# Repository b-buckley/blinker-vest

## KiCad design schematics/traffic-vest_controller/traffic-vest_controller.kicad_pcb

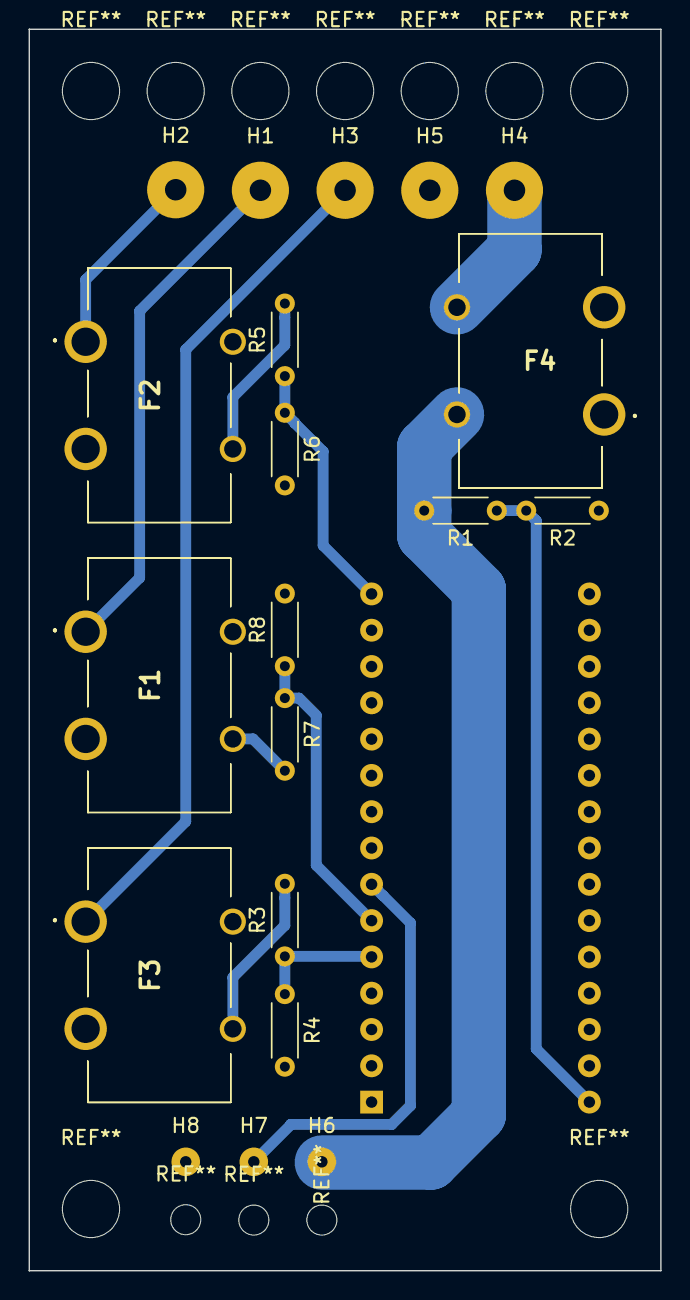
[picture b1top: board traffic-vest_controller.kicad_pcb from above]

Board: 2 copper layers, 44.2 x 86.9 mm, 21 parts (1 on the bottom side), 14 nets.

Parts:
A1: Arduino_Nano_v3.x; Arduino_Nano
F1, F2, F3: 1A; 35492
F4: 7.5A; 35492
H1: Bike Left; SolderWirePad_1x01_Drill1.5mm
H2: Bike Brake; SolderWirePad_1x01_Drill1.5mm
H3: Bike Right; SolderWirePad_1x01_Drill1.5mm
H4: Bike Power; SolderWirePad_1x01_Drill1.5mm
H5: Bike Ground; SolderWirePad_1x01_Drill1.5mm
H6: LED +12V; SolderWirePad_1x01_Drill0.8mm
H7: LED Data; SolderWirePad_1x01_Drill0.8mm
H8: LED GND; SolderWirePad_1x01_Drill0.8mm
R1: 100; R_Axial_DIN0204_L3.6mm_D1.6mm_P5.08mm_Horizontal
R2: 300; R_Axial_DIN0204_L3.6mm_D1.6mm_P5.08mm_Horizontal
R3, R5, R7: 20k; R_Axial_DIN0204_L3.6mm_D1.6mm_P5.08mm_Horizontal
R4, R6, R8: 10k; R_Axial_DIN0204_L3.6mm_D1.6mm_P5.08mm_Horizontal

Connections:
GNDREF: A1.4, A1.29, H5.1, H8.1, R2.1, R4.2, R6.2, R8.2
unnamed: A1.5, R3.1, R4.1
unnamed: A1.6, R7.1, R8.1
unnamed: A1.7, H7.1
unnamed: A1.15, R5.1, R6.1
unnamed: A1.30, R1.1, R2.2
unnamed: F1.1, H1.1
unnamed: F1.3, R7.2
unnamed: F2.1, H2.1
unnamed: F2.3, R5.2
unnamed: F3.1, H3.1
unnamed: F3.3, R3.2
unnamed: F4.3, H4.1
unnamed: F4.4, H6.1, R1.2

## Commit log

2022-02-21 Initial commit of code repo for Traffic Vest project for ELT-2720
2022-02-21 just playing with git
2022-03-09 Better late than never to start version tracking and stop sweating about version numbers
2022-03-09 Re-organized file tree, fixed paths in kidcad files, etc.
2022-03-09 added .gitignore
2022-03-10 Converted physical connectors to mounting holes; need to resize holes in PCB for wire sizes and spacing
2022-03-15 first add of schematics b/c of cached submodule weirdness. Includes updates as of converting connectors/mounting holes to generic pins with THT solder holes and matching strain-relief NPTHs. Also rea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
2022-03-15 Added dirty separate handling for each input signal as proof-of-concept.
2022-03-16 expanded board footprint to accomodate corner mounting holes; rearranged fuses and pins for left/right to D2, D3 for external interrupts; fixed orientation of fuse clips
2022-03-16 Routed tracks and added ground pour. Potentially finished PCB layout!
2022-03-16 Minor track tweaks
2022-03-16 More minor track tweaks
2022-03-17 moved copper to back of PCB, flipped fuse clips, rerouted tracks, refilled copper pour
2022-03-24 Flipped nano, rearranged digital pin connecctions, futzed with connection spacing, re-routed tracks
2022-03-24 Began writing firmware in earnest: Brake output runs on a timer interrupt, turn signals on hardware interrupts. Need to finish implementing overall flow.
2022-03-29 Fixed ground pour to make contiguous zone. One more rearrangement of circuits to pins for cleanliness and short tracks. Generated gerbers and drill file for cutting.
2022-03-29 Isolated (left) animation within leftFrameHandler(). Timer set-up is now calculated from FREQUENCY macro instead of hard-coded.
2022-04-07 Board V3, child of V1: \n* Corrected orientation of nano\n* Re-ran tracks\n* Incorporated V2 improvements: wire drill hole sizes, extra spacing between mount and relief holes, name and course etched 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
2022-04-23 Added ./site for project website
2022-04-23 did it add ./site?
2022-04-23 Set theme jekyll-theme-midnight
2022-04-23 hopefully adding jekyll site for github pages?
2022-04-23 trying to clean up branches for jekyull and github pages
2022-04-23 still trying to clean up jekyll and github pages
2022-04-23 github pages, hello world
2022-04-23 this is endless
2022-04-23 once more attempting to initialize github pages site
2022-04-23 theme applied
2022-04-23 fiddling with paths
2022-04-23 fiddling with paths 2
2022-04-23 more fiddling
2022-04-23 trying. yet. again.
2022-04-23 why doesn't jekyll work after push?
2022-04-23 trying yet again to get this site in the right place
2022-04-23 bleh, again
2022-04-23 still pecking at github sites and jekyll theming
2022-04-23 i think maybe it's working now?
2022-04-23 clean up on main
2022-04-23 more cleanup
2022-04-24 Minimal mistakes with remote theme, added placeholders for pages, added custom _data/navigation.yml, set dark skin and defaults for _pages
2022-04-26 Home page built out, jekyll brought up to a point ready for content. Processed and added lots of project images
2022-04-26 clean-up
2022-04-26 added jekyll-include-cached to plugins in _config.yml for GH pages
2022-04-26 fixed jekyll-include-cache?
2022-04-26 fixed jekyll-include-cache? again?
2022-04-26 Began filling in 'I&P' page, finished 'Inspiration' portion.
2022-04-27 I&P finished, started Circuit. Pausing to see about arduino-cli user directories and consolidating the code repo into this one.
2022-04-27 prepping for merge, maybe
2022-04-27 double-down on that merge
2022-04-27 some directory cleanup
2022-04-27 First pass at Circuit page finished.
2022-04-27 Fixed a few broken links, fiddled with author bio in _config.yaml
2022-04-27 asdf
2022-05-01 Begun populating hardware.md
2022-05-01 minor commit
2022-05-01 more work on the hardware pages; also image prep
2022-05-02 'Finished' hardware page... lots of images! Also first drafted up the software page. I should add code blocks and get those state diagrams in there, but important and links are there.
2022-05-02 Fixed a single missing 'i'
2022-05-02 Spent the day working on the slides for the final presentation
2022-05-02 still trying to get rib of fat presentation
2022-05-02 deleted large video file, re-instated shrunken final presentation file
2022-05-03 Added images to /software/, also minor corrections throughout
2022-05-07 added board process images
2022-05-07 added board design images
2022-05-13 User Manual and Technical Report added to /reports
